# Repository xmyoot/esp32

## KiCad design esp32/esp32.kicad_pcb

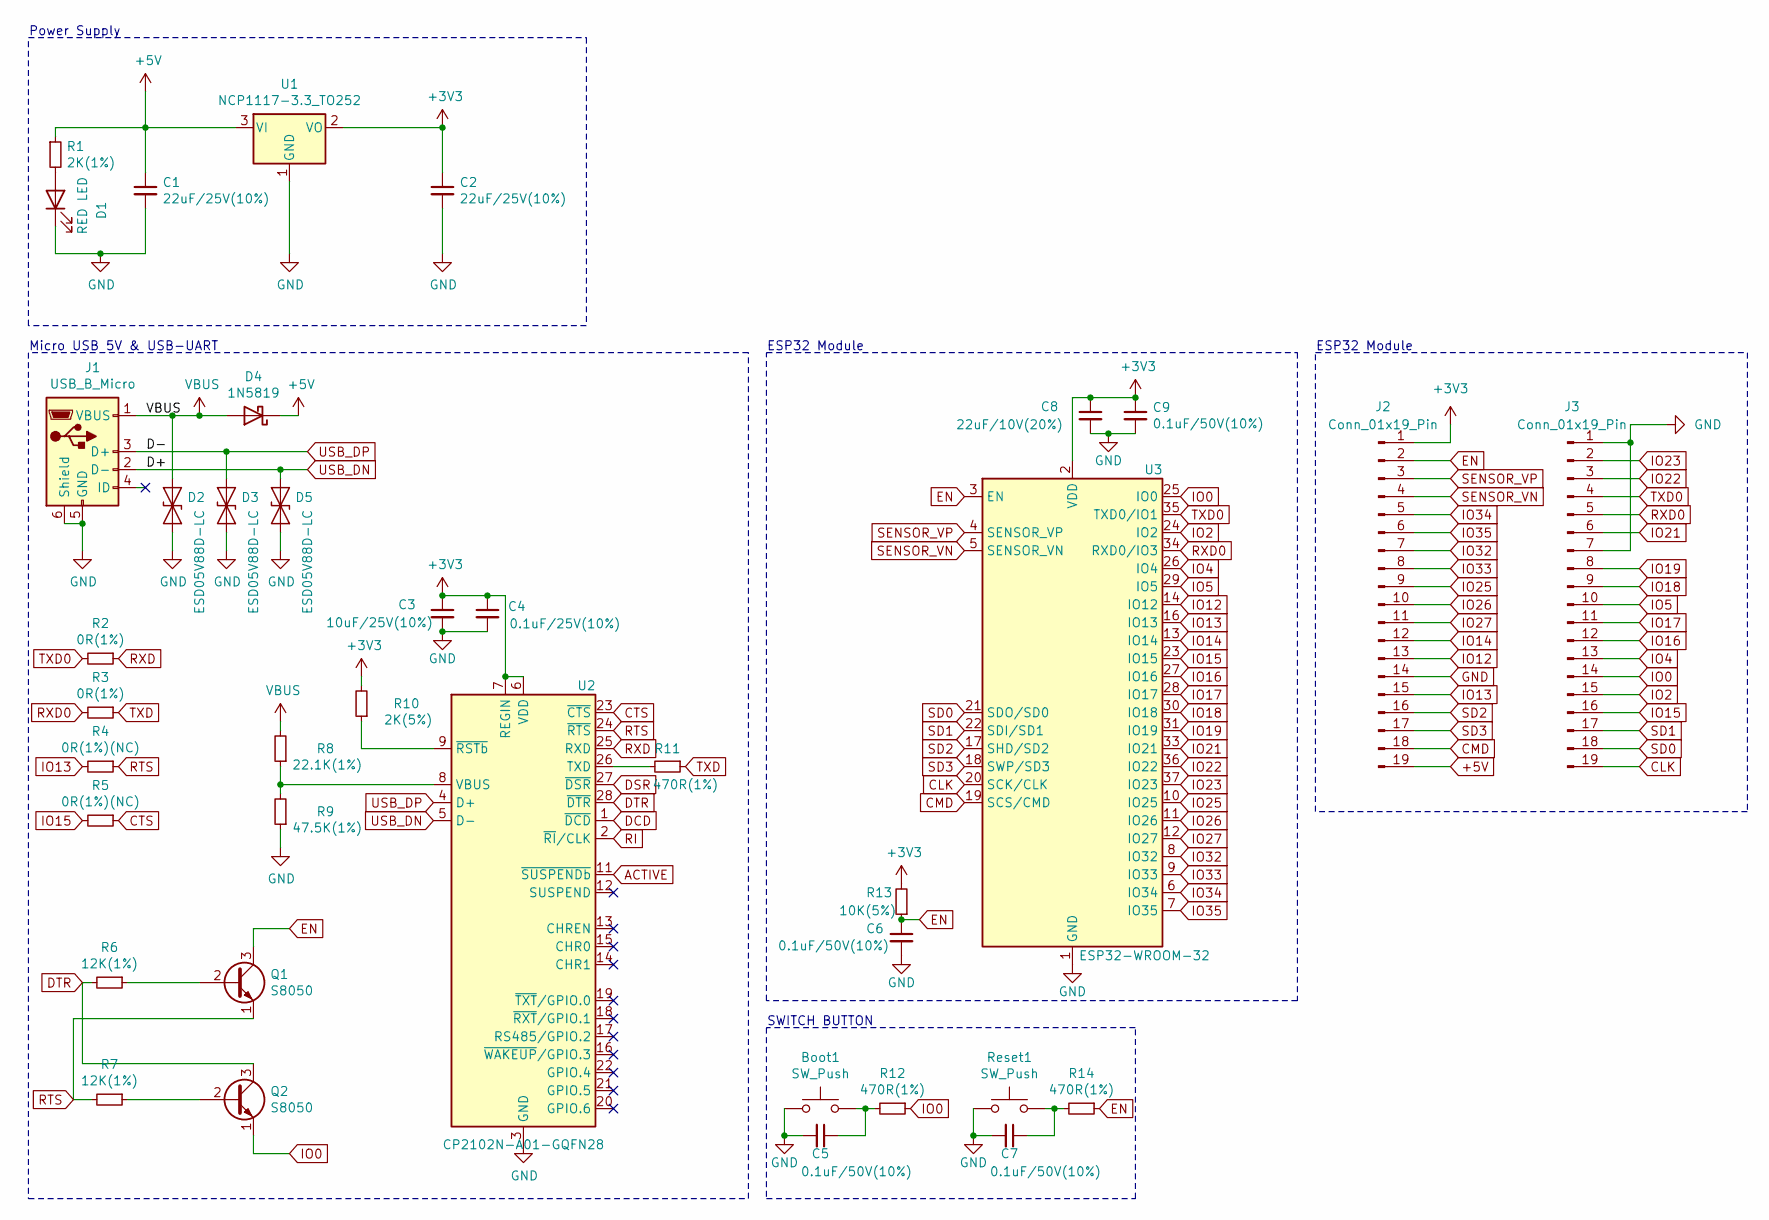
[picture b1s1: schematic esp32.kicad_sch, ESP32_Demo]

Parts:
Boot1: SW_Push; SW_Push_SPST_NO_Alps_SKRK
C1, C2: 22uF/25V(10%); C_0603_1608Metric
C3: 10uF/25V(10%); C_0603_1608Metric
C4: 0.1uF/25V(10%); C_0402_1005Metric
C5, C6, C7, C9: 0.1uF/50V(10%); C_0402_1005Metric
C8: 22uF/10V(20%); C_0603_1608Metric
D1: RED LED; LED_0603_1608Metric
D2, D3, D5: ESD05V88D-LC; D_SOD-923
D4: 1N5819; D_0402_1005Metric
J1: USB_B_Micro; USB_Micro-B_Molex_47346-0001
J2, J3: Conn_01x19_Pin; PinHeader_1x19_P1.00mm_Vertical
Q1, Q2: S8050; SOT-23
R1: 2K(1%); R_0402_1005Metric
R2, R3: 0R(1%); R_0402_1005Metric
R4, R5: 0R(1%)(NC); R_0402_1005Metric
R6, R7: 12K(1%); R_0402_1005Metric
R8: 22.1K(1%); R_0402_1005Metric
R9: 47.5K(1%); R_0402_1005Metric
R10: 2K(5%); R_0402_1005Metric
R11: 470R(1%); C_0402_1005Metric
R12, R14: 470R(1%); R_0402_1005Metric
R13: 10K(5%); R_0402_1005Metric
Reset1: SW_Push; SW_Push_SPST_NO_Alps_SKRK
U1: NCP1117-3.3_TO252; SOT-223
U2: CP2102N-A01-GQFN28; QFN-28-1EP_5x5mm_P0.5mm_EP3.35x3.35mm
U3: ESP32-WROOM-32

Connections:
+3V3: C2.1, C3.1, C4.1, C8.1, C9.1, J2.1, R10.2, R13.2, U1.2 (VO), U2.6 (VDD), U2.7 (REGIN), U3.2 (VDD)
+5V: C1.1, D4.1 (K), J2.19, R1.1, U1.3 (VI)
ACTIVE: U2.11 (~SUSPENDb)
CLK: J3.19, U3.20 (SCK/CLK)
CMD: J2.18, U3.19 (SCS/CMD)
CTS: R5.1, U2.23 (~CTS)
DCD: U2.1 (~DCD)
DSR: U2.27 (~DSR)
DTR: Q2.3 (C), R6.2, U2.28 (~DTR)
EN: C6.1, J2.2, Q1.3 (C), R13.1, R14.1, U3.3 (EN)
GND: Boot1.1, C1.2, C2.2, C3.2, C4.2, C5.2, C6.2, C7.2, C8.2, C9.2, D1.1 (K), D2.2 (A2), D3.2 (A2), D5.2 (A2), J1.5 (GND), J1.6 (Shield), J2.14, J3.1, J3.7, R9.1, Reset1.1, U1.1 (GND), U2.3 (GND), U2.29 (GND), U3.1 (GND), U3.15 (GND), U3.38 (GND), U3.39 (GND)
IO0: J3.14, Q2.1 (E), R12.1, U3.25 (IO0)
IO2: J3.15, U3.24 (IO2)
IO4: J3.13, U3.26 (IO4)
IO5: J3.10, U3.29 (IO5)
IO12: J2.13, U3.14 (IO12)
IO13: J2.15, R4.2, U3.16 (IO13)
IO14: J2.12, U3.13 (IO14)
IO15: J3.16, R5.2, U3.23 (IO15)
IO16: J3.12, U3.27 (IO16)
IO17: J3.11, U3.28 (IO17)
IO18: J3.9, U3.30 (IO18)
IO19: J3.8, U3.31 (IO19)
IO21: J3.6, U3.33 (IO21)
IO22: J3.3, U3.36 (IO22)
IO23: J3.2, U3.37 (IO23)
IO25: J2.9, U3.10 (IO25)
IO26: J2.10, U3.11 (IO26)
IO27: J2.11, U3.12 (IO27)
IO32: J2.7, U3.8 (IO32)
IO33: J2.8, U3.9 (IO33)
IO34: J2.5, U3.6 (IO34)
IO35: J2.6, U3.7 (IO35)
unnamed: Boot1.2, C5.1, R12.2
unnamed: C7.1, R14.2, Reset1.2
unnamed: D1.2 (A), R1.2
unnamed: Q1.2 (B), R6.1
unnamed: Q2.2 (B), R7.1
unnamed: R11.2, U2.26 (TXD)
unnamed: R8.1, R9.2, U2.8 (VBUS)
unnamed: R10.1, U2.9 (~RSTb)
RI: U2.2 (~RI/CLK)
RTS: Q1.1 (E), R4.1, R7.2, U2.24 (~RTS)
RXD: R2.1, U2.25 (RXD)
RXD0: J3.5, R3.2, U3.34 (RXD0/IO3)
SD0: J3.18, U3.21 (SDO/SD0)
SD1: J3.17, U3.22 (SDI/SD1)
SD2: J2.16, U3.17 (SHD/SD2)
SD3: J2.17, U3.18 (SWP/SD3)
SENSOR_VN: J2.4, U3.5 (SENSOR_VN)
SENSOR_VP: J2.3, U3.4 (SENSOR_VP)
TXD: R3.1, R11.1
TXD0: J3.4, R2.2, U3.35 (TXD0/IO1)
USB_DN: D5.1 (A1), J1.2 (D-), U2.5 (D-)
USB_DP: D3.1 (A1), J1.3 (D+), U2.4 (D+)
VBUS: D2.1 (A1), D4.2 (A), J1.1 (VBUS), R8.2

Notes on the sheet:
ESP32 Module
SWITCH BUTTON
Power Supply
Micro USB 5V & USB-UART

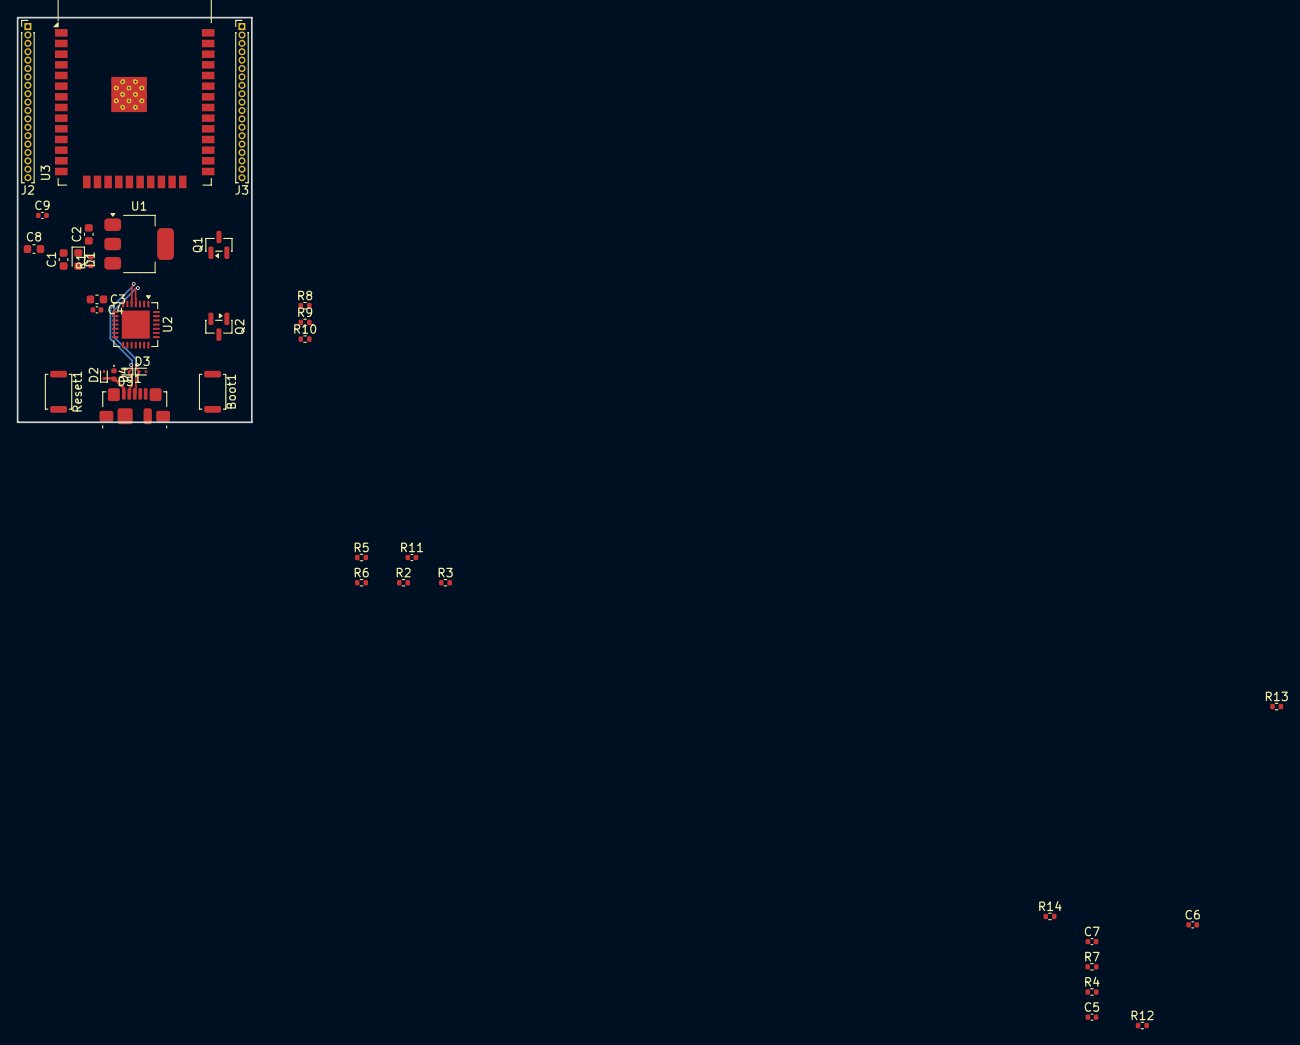
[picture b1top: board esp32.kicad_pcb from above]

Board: 2 copper layers, 27.9 x 48.2 mm, 38 parts (0 on the bottom side), 52 nets.

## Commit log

2026-04-22 updated to DevKitC schematic per Espressif docs
2026-04-24 usb routing
